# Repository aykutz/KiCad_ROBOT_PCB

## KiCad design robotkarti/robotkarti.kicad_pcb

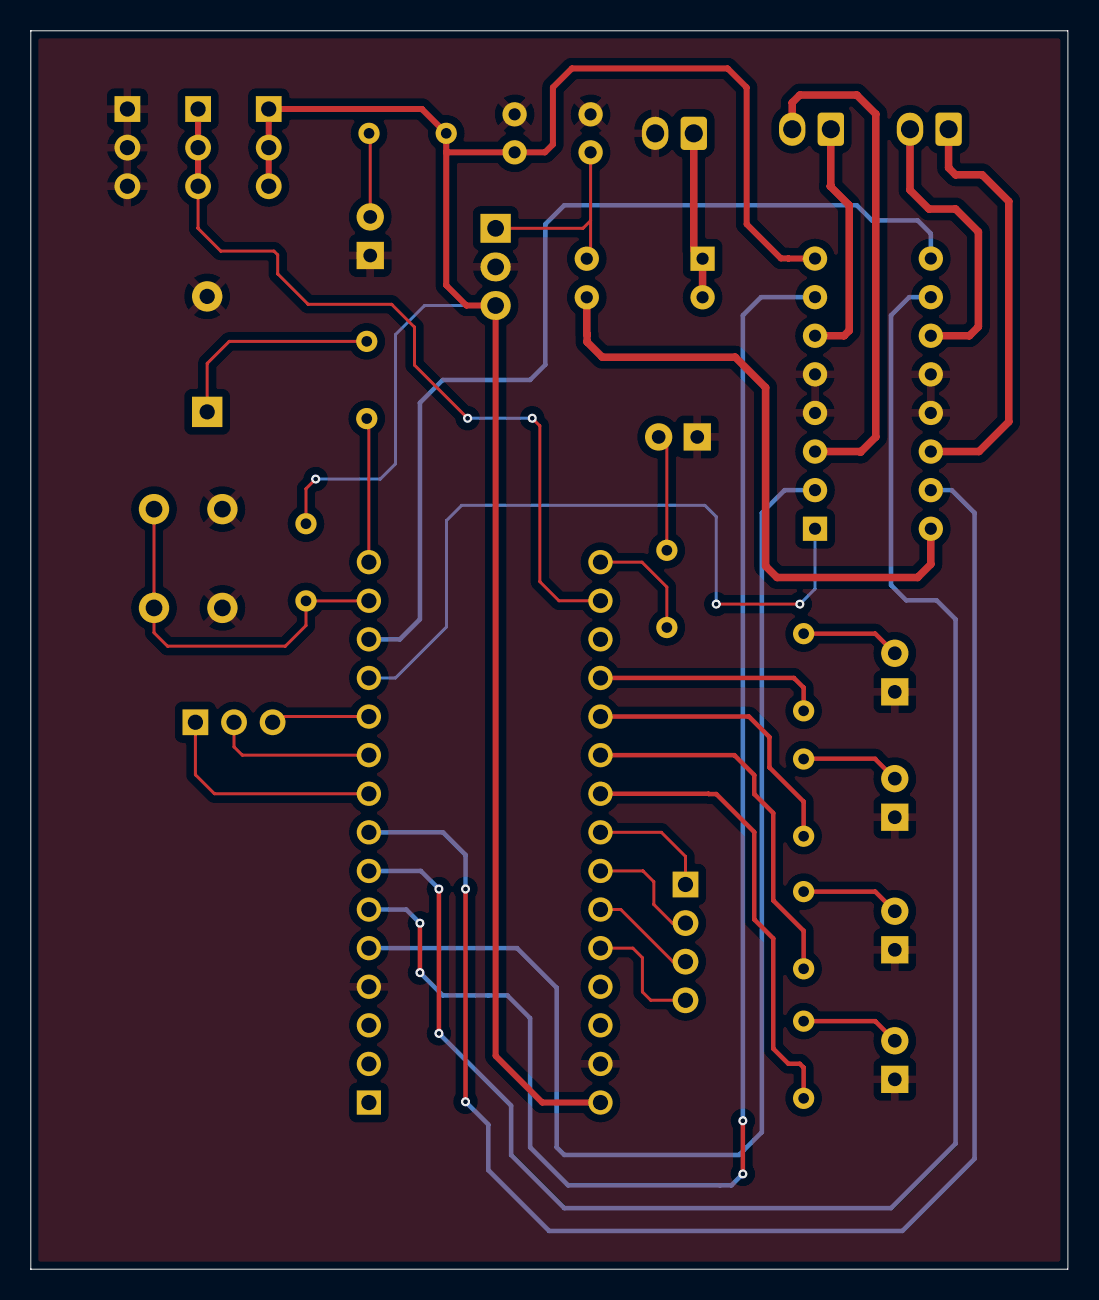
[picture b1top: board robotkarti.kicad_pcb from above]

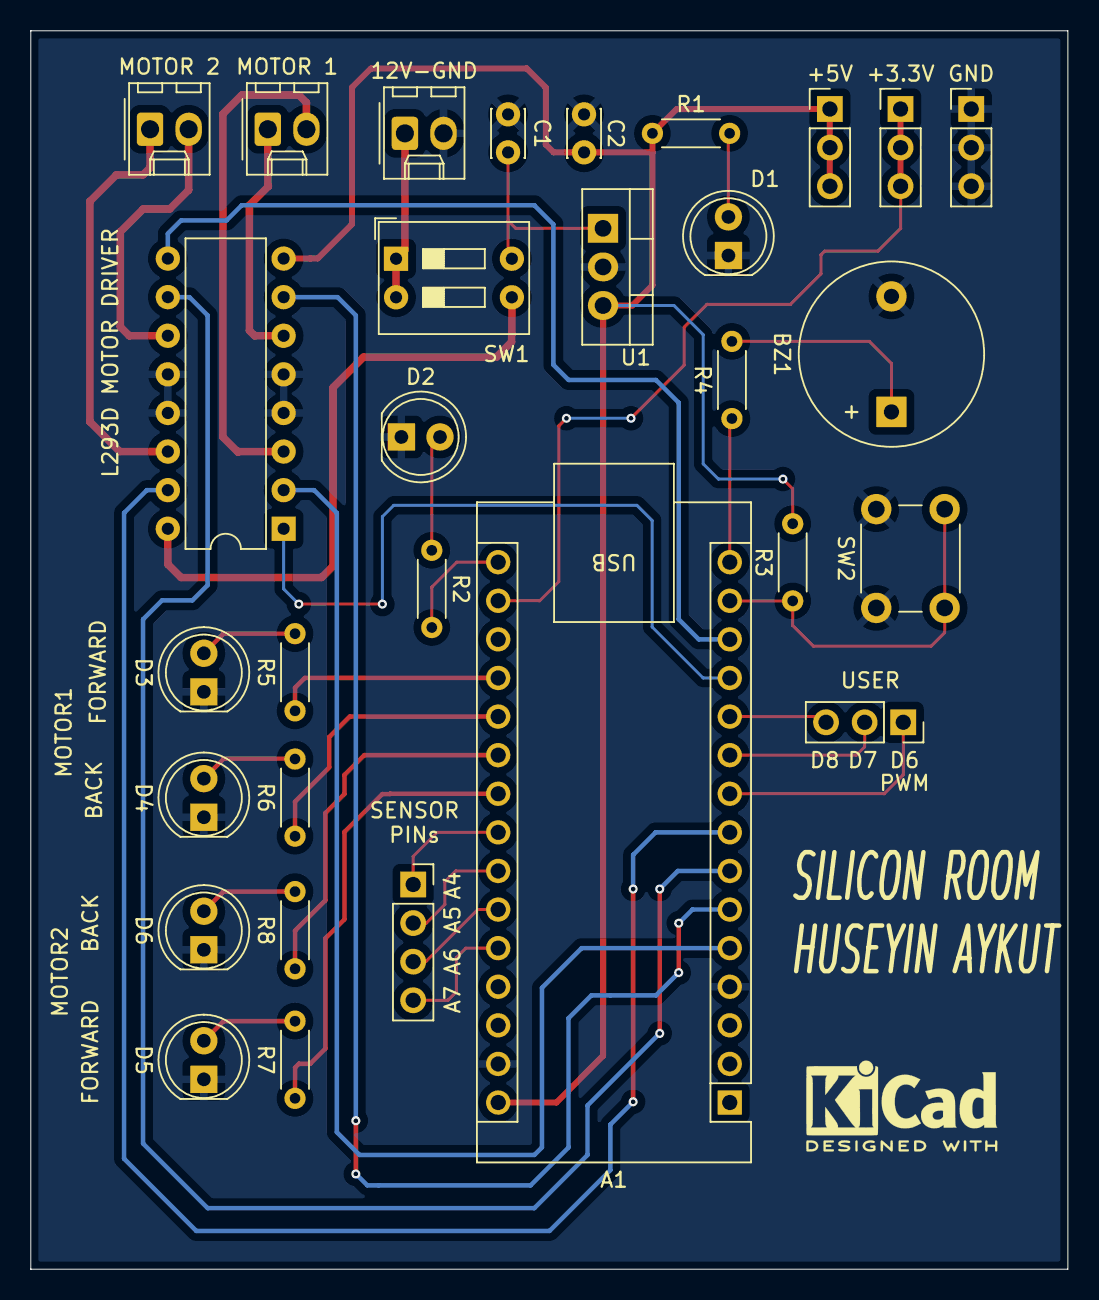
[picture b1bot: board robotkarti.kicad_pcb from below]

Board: 2 copper layers, 68.2 x 81.5 mm, 30 parts (30 on the bottom side), 37 nets.

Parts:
12V-GND: pwr; Molex_KK-254_AE-6410-02A_1x02_P2.54mm_Vertical
+3.3V: +3.3V; PinHeader_1x03_P2.54mm_Vertical
+5V: +5V; PinHeader_1x03_P2.54mm_Vertical
A1: Arduino_Nano_v3.x; Arduino_Nano
BZ1: Buzzer; Buzzer_12x9.5RM7.6
C1: 0.33uF; C_Disc_D3.0mm_W2.0mm_P2.50mm
C2: 0.1uF; C_Disc_D3.0mm_W2.0mm_P2.50mm
D1, D2, D3, D4, D5, D6: LED; LED_D5.0mm
GND: GND; PinHeader_1x03_P2.54mm_Vertical
J8: SENSORs; PinSocket_1x04_P2.54mm_Vertical
MOTOR 1: MOTOR1; Molex_KK-254_AE-6410-02A_1x02_P2.54mm_Vertical
MOTOR 2: MOTOR2; Molex_KK-254_AE-6410-02A_1x02_P2.54mm_Vertical
R1, R2, R4, R5, R6, R7, R8: 330; R_Axial_DIN0204_L3.6mm_D1.6mm_P5.08mm_Horizontal
R3: 10K; R_Axial_DIN0204_L3.6mm_D1.6mm_P5.08mm_Horizontal
SW1: switch; SW_DIP_SPSTx02_Slide_9.78x7.26mm_W7.62mm_P2.54mm
SW2: SW_PUSH_6mm_H4.3mm
U1: LM7805_TO220; TO-220-3_Vertical
U2: L293D; DIP-16_W7.62mm
USER: USER PINs; PinSocket_1x03_P2.54mm_Vertical

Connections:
3.3V_OUT: +3.3V.1, +3.3V.2, +3.3V.3, A1.17 (3V3)
5V_OUT: +5V.1, +5V.2, +5V.3, A1.30 (VIN), C2.1, R1.1, R3.2, U1.3 (VO), U2.8 (VCC2)
12V_OUT: SW1.3, U2.16 (VCC1)
+12V: 12V-GND.1, SW1.1, SW1.2
BUTTON: A1.14 (D11), R3.1, SW2.2
BUZZER: A1.15 (D12), R4.1
GND: 12V-GND.2, A1.4 (GND), A1.29 (GND), BZ1.2 (-), C1.2, C2.2, D1.1 (K), D2.1 (K), D3.1 (K), D4.1 (K), D5.1 (K), D6.1 (K), GND.1, GND.2, GND.3, SW2.1, U1.2 (GND), U2.4 (GND), U2.5 (GND), U2.12 (GND), U2.13 (GND)
LED: A1.16 (D13), R2.2
M1B_LED: A1.20 (A1), R6.1
M1F_LED: A1.19 (A0), R5.1
M2B_LED: A1.22 (A3), R7.1
M2F_LED: A1.21 (A2), R8.1
MOTOR1_BACK: A1.6 (D3), U2.7 (2A)
MOTOR1_FORWARD: A1.5 (D2), U2.2 (1A)
MOTOR1_PWM: A1.12 (D9), U2.1 (EN1,2)
MOTOR2_BACK: A1.8 (D5), U2.15 (4A)
MOTOR2_FORWARD: A1.7 (D4), U2.10 (3A)
MOTOR2_PWM: A1.13 (D10), U2.9 (EN3,4)
unnamed: BZ1.1 (+), R4.2
unnamed: D1.2 (A), R1.2
unnamed: D2.2 (A), R2.1
unnamed: D3.2 (A), R5.2
unnamed: D4.2 (A), R6.2
unnamed: D5.2 (A), R7.2
unnamed: D6.2 (A), R8.2
unnamed: MOTOR 1.1, U2.6 (2Y)
unnamed: MOTOR 1.2, U2.3 (1Y)
unnamed: MOTOR 2.1, U2.14 (4Y)
unnamed: MOTOR 2.2, U2.11 (3Y)
unnamed: C1.1, SW1.4, U1.1 (VI)
SENSOR1: A1.23 (A4), J8.1
SENSOR2: A1.24 (A5), J8.2
SENSOR3: A1.25 (A6), J8.3
SENSOR4: A1.26 (A7), J8.4
USER_IO_1: A1.10 (D7), USER.2
USER_IO_2: A1.11 (D8), USER.3
USER_PWM: A1.9 (D6), USER.1

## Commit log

2024-10-19 KiCad_ROBOT_PCB
